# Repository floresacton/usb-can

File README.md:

# usb-can
USB to CAN FD bidirectional converter

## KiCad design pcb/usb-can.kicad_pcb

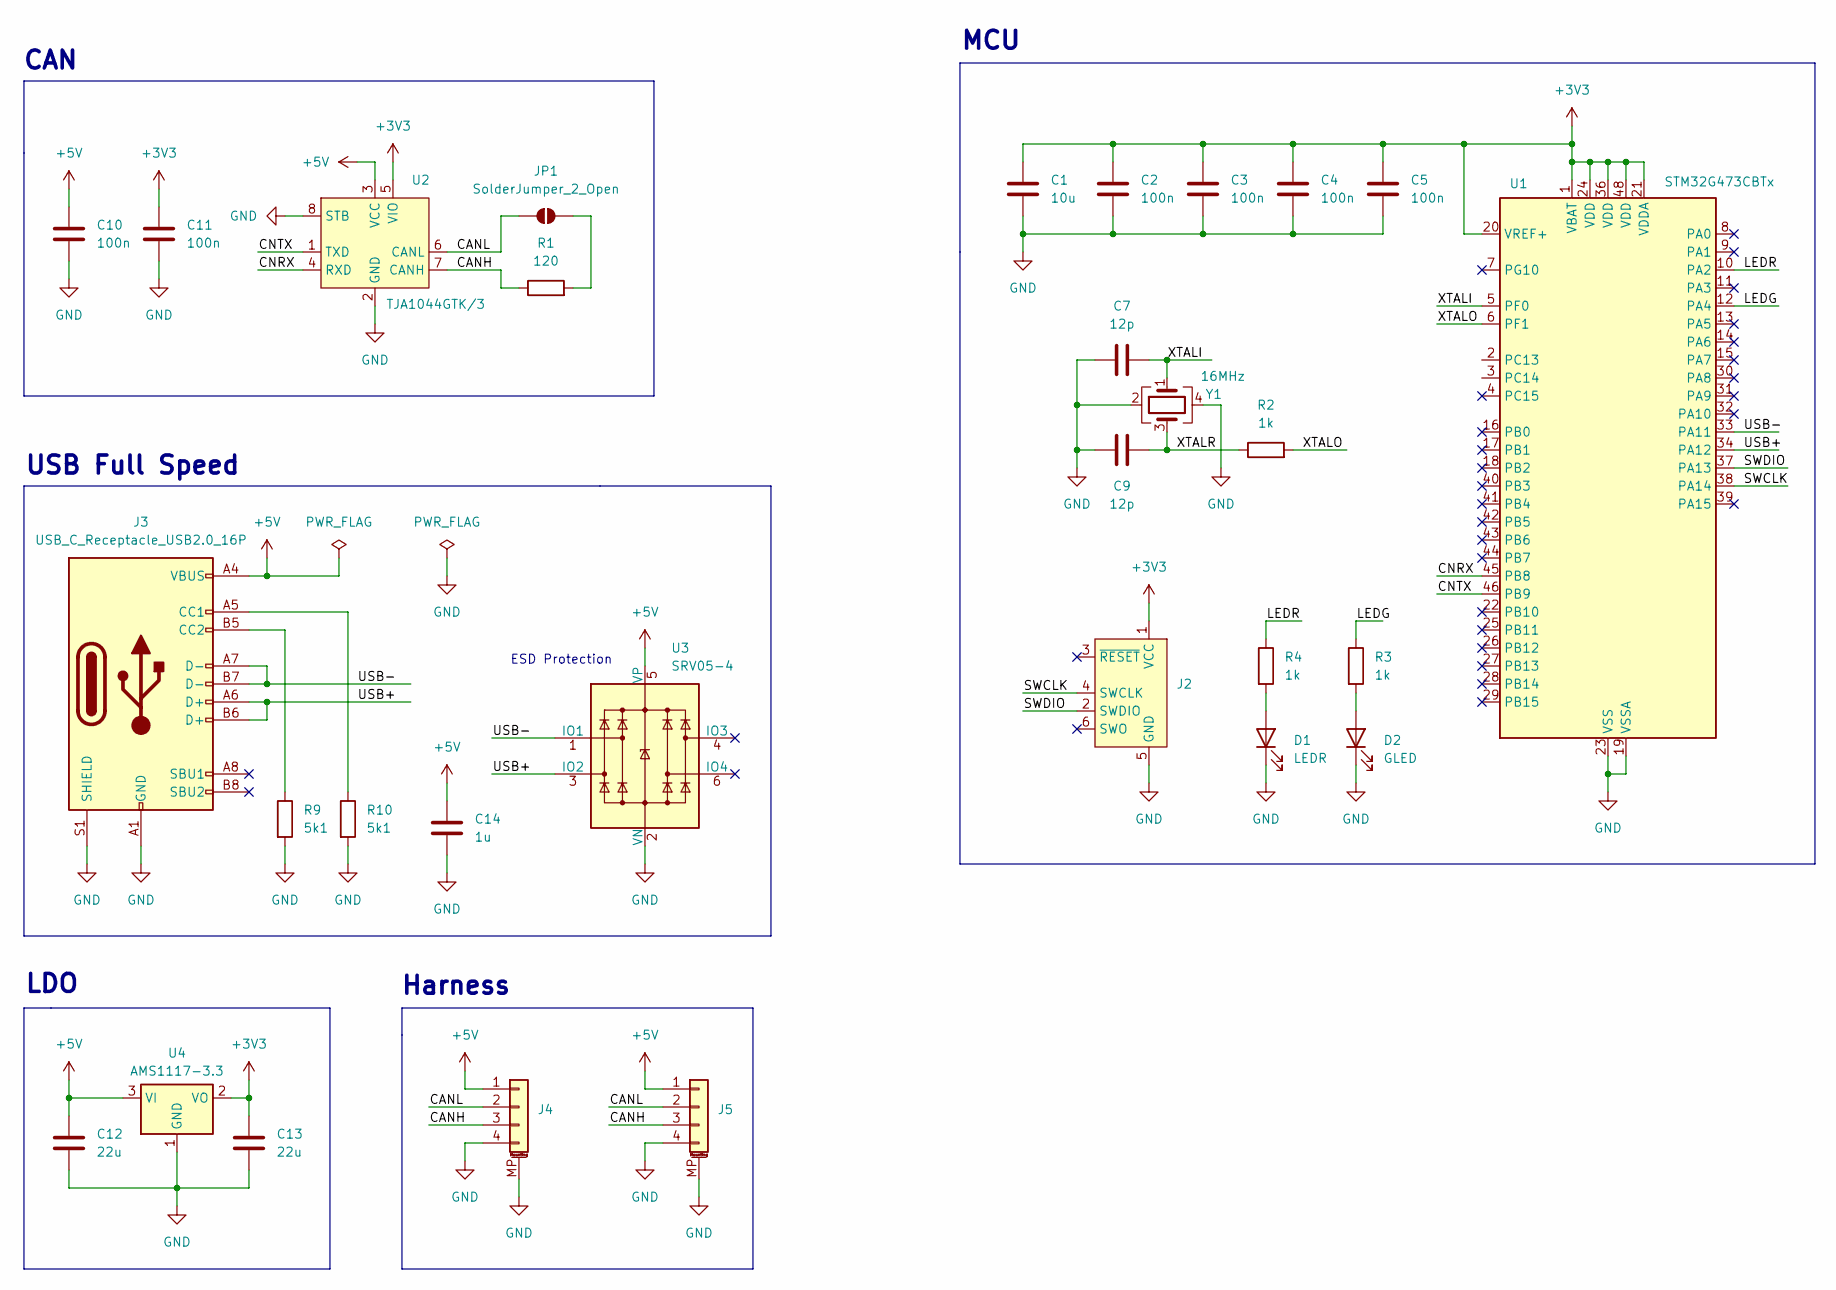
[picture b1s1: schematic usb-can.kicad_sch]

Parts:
C1: 10u; C_0402_1005Metric; LCSC C15525
C2, C3, C4, C5, C10, C11: 100n; C_0402_1005Metric; LCSC C1525
C7, C9: 12p; C_0402_1005Metric; LCSC C1547
C12: 22u; C_0805_2012Metric; LCSC C45783
C13: 22u; C_0603_1608Metric; LCSC C59461
C14: 1u; C_0402_1005Metric; LCSC C52923
D1: LEDR; LED_0603_1608Metric; LCSC C2286
D2: GLED; LED_0603_1608Metric; LCSC C72043
J2: Conn_ARM_SWD_TagConnect_TC2030-NL; Tag-Connect_TC2030-IDC-NL_2x03_P1.27mm_Vertical
J3: USB_C_Receptacle_USB2.0_16P; USB_C_Receptacle_GCT_USB4105-xx-A_16P_TopMnt_Horizontal; LCSC C2765186
J4, J5: Conn_01x04_MountingPin; JST_GH_SM04B-GHS-TB_1x04-1MP_P1.25mm_Horizontal; LCSC C189895
JP1: SolderJumper_2_Open; SolderJumper-2_P1.3mm_Open_RoundedPad1.0x1.5mm
R1: 120; R_1206_3216Metric; LCSC C17909
R2, R3, R4: 1k; R_0402_1005Metric; LCSC C11702
R9, R10: 5k1; R_0402_1005Metric; LCSC C25905
U1: STM32G473CBTx; LQFP-48_7x7mm_P0.5mm; LCSC C730111
U2: TJA1044GTK/3; HVSON-8-1EP_3x3mm_P0.65mm_EP1.6x2.4mm; LCSC C2157795
U3: SRV05-4; SOT-23-6; LCSC C7420376
U4: AMS1117-3.3; SOT-223-3_TabPin2; LCSC C6186
Y1: 16MHz; Crystal_SMD_3225-4Pin_3.2x2.5mm; LCSC C13738

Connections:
+3V3: C1.1, C2.1, C3.1, C4.1, C5.1, C11.1, C13.1, J2.1 (VCC), U1.1 (VBAT), U1.20 (VREF+), U1.21 (VDDA), U1.24 (VDD), U1.36 (VDD), U1.48 (VDD), U2.5 (VIO), U4.2 (VO)
+5V: C10.1, C12.1, C14.1, J3.A4 (VBUS), J3.A9 (VBUS), J3.B4 (VBUS), J3.B9 (VBUS), J4.1, J5.1, U2.3 (VCC), U3.5 (VP), U4.3 (VI)
/CANH: J4.3, J5.3, R1.1, U2.7 (CANH)
/CANL: J4.2, J5.2, JP1.1 (A), U2.6 (CANL)
/CNRX: U1.45 (PB8), U2.4 (RXD)
/CNTX: U1.46 (PB9), U2.1 (TXD)
/LEDG: R3.1, U1.12 (PA4)
/LEDR: R4.1, U1.10 (PA2)
/SWCLK: J2.4 (SWCLK), U1.38 (PA14)
/SWDIO: J2.2 (SWDIO), U1.37 (PA13)
/USB+: J3.A6 (D+), J3.B6 (D+), U1.34 (PA12), U3.3 (IO2)
/USB-: J3.A7 (D-), J3.B7 (D-), U1.33 (PA11), U3.1 (IO1)
/XTALI: C7.2, U1.5 (PF0), Y1.1
/XTALO: R2.2, U1.6 (PF1)
/XTALR: C9.2, R2.1, Y1.3
GND: C1.2, C2.2, C3.2, C4.2, C5.2, C7.1, C9.1, C10.2, C11.2, C12.2, C13.2, C14.2, D1.1 (K), D2.1 (K), J2.5 (GND), J3.A1 (GND), J3.A12 (GND), J3.B1 (GND), J3.B12 (GND), J3.S1 (SHIELD), J4.4, J4.MP (MountPin), J5.4, J5.MP (MountPin), R9.2, R10.2, U1.19 (VSSA), U1.23 (VSS), U1.35 (VSS), U1.47 (VSS), U2.2 (GND), U2.8 (STB), U2.9 (EPAD), U3.2 (VN), U4.1 (GND), Y1.2, Y1.4
unnamed: D1.2 (A), R4.2
unnamed: D2.2 (A), R3.2
unnamed: J3.A5 (CC1), R10.1
unnamed: J3.B5 (CC2), R9.1
unnamed: JP1.2 (B), R1.2

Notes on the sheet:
ESD Protection
MCU
LDO
CAN
Harness
USB Full Speed

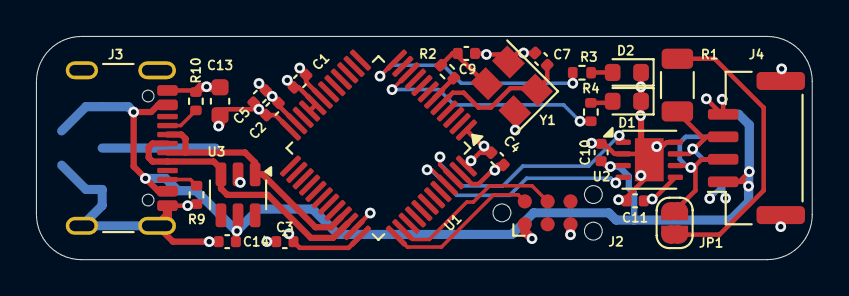
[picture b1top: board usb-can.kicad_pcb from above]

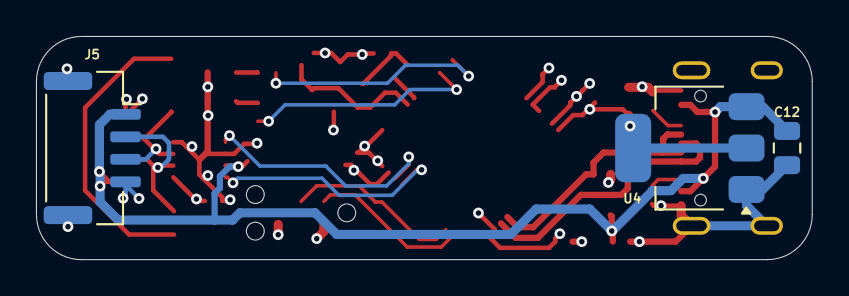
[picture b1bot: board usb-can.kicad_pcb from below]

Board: 4 copper layers, 43.1 x 12.4 mm, 30 parts (3 on the bottom side), 21 nets.

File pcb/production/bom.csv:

Designator,Footprint,Quantity,Value,LCSC Part #
C1,0402,1,10u,C15525
"C10, C11, C2, C3, C4, C5",0402,6,100n,C1525
C12,0805,1,22u,C45783
C13,0603,1,22u,C59461
C14,0402,1,1u,C52923
"C7, C9",0402,2,12p,C1547
D1,0603,1,LEDR,C2286
D2,0603,1,GLED,C72043
J3,USB_C_Receptacle_GCT_USB4105-xx-A_16P_TopMnt_Horizontal,1,USB_C_Receptacle_USB2.0_16P,C2765186
"J4, J5",JST_GH_SM04B-GHS-TB_1x04-1MP_P1.25mm_Horizontal,2,Conn_01x04_MountingPin,C189895
R1,1206,1,120,C17909
"R10, R9",0402,2,5k1,C25905
"R2, R3, R4",0402,3,1k,C11702
U1,LQFP-48_7x7mm_P0.5mm,1,STM32G473CBTx,C730111
U2,HVSON-8-1EP_3x3mm_P0.65mm_EP1.6x2.4mm,1,TJA1044GTK/3,C2157795
U3,SOT-23-6,1,SRV05-4,C7420376
U4,SOT-223-3_TabPin2,1,AMS1117-3.3,C6186
Y1,Crystal_SMD_3225-4Pin_3.2x2.5mm,1,16MHz,C13738

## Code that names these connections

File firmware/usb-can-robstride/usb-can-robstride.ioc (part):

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Mcu.Name=STM32G473C(B-C-E)Tx
Mcu.Package=LQFP48
Mcu.UserName=STM32G473CBTx
PA11.Mode=Device
PA11.Signal=USB_DM
PA12.Mode=Device
PA12.Signal=USB_DP
PA13.Mode=Serial_Wire
PA13.Signal=SYS_JTMS-SWDIO
PA14.Mode=Serial_Wire
PA14.Signal=SYS_JTCK-SWCLK
PA2.GPIOParameters=GPIO_Label
PA2.GPIO_Label=LEDR
PA2.Signal=GPIO_Output
PA4.GPIOParameters=GPIO_Label
PA4.GPIO_Label=LEDG
PA4.Signal=GPIO_Output
PB8-BOOT0.Mode=FDCAN_Activate
PB8-BOOT0.Signal=FDCAN1_RX
PB9.Mode=FDCAN_Activate
PB9.Signal=FDCAN1_TX
PF0-OSC_IN.Mode=HSE-External-Oscillator
PF0-OSC_IN.Signal=RCC_OSC_IN
PF1-OSC_OUT.Mode=HSE-External-Oscillator
PF1-OSC_OUT.Signal=RCC_OSC_OUT
RCC.HSE_VALUE=16000000
RCC.SYSCLKFreq_VALUE=144000000
RCC.SYSCLKSource=RCC_SYSCLKSOURCE_PLLCLK
board=custom

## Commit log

2024-06-13 Add readme
2024-06-13 Add gitignore
2024-06-26 Transfer project
2024-06-26 Setup repo
2024-06-26 Ignore FATFS
2024-06-26 Setup ioc
2024-07-17 Send and receive dynamic sizes
2024-07-17 Send and receive dynamic sized frames
2024-07-17 Change status led function
2024-07-19 Rough setup for testing brush-can project
2024-09-04 Update interface software
2024-10-14 Minimize schematic
2024-12-11 Finish rev2
2025-05-05 Save
2025-07-17 Save robstride test
2025-09-29 Update to kicad 9
2025-10-06 Init new usb-can firmware
2025-10-06 Add USB_Device
2025-10-07 Update usb-can
2025-10-07 Remove test snippet
2025-10-07 Add rust plotter
2025-10-30 Move plotter
2025-10-30 Init rust firmware
2025-10-30 Add clock config
